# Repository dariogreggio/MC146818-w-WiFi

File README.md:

# MC146818-w-WiFi
a small board, pin compatible to MC146818 RTC, featuring WiFi for retrieving time!

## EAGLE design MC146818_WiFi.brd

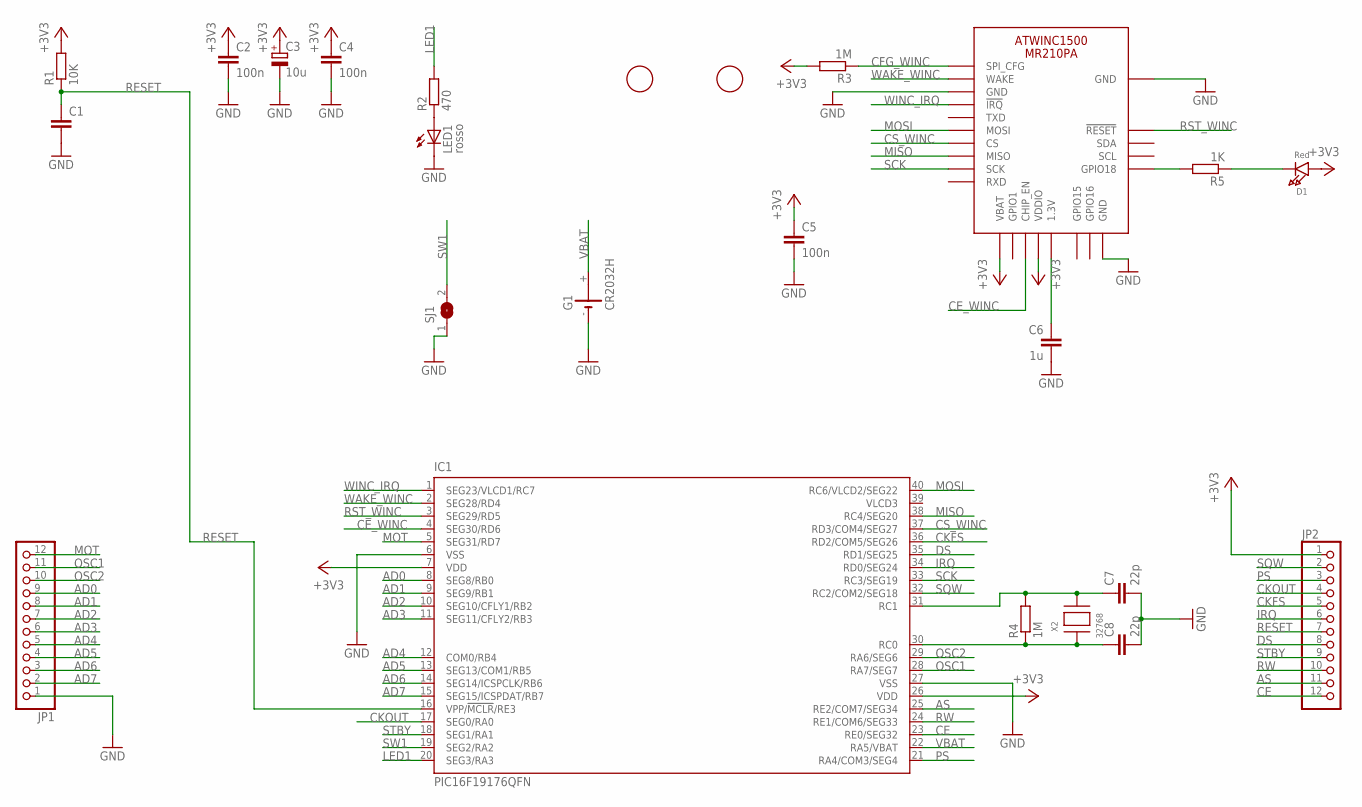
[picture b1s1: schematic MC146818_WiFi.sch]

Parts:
C1: C-EUC0603; C0603
C2, C4, C5: 100n; C0603
C3: 10u; SMC_Z
C6: 1u; C0805
C7, C8: 22p; C0603
D1: Red; CHIPLED_0805_NOOUTLINE
F1, F2: FIDUCIAL; FIDUCIAL_1MM
G1: CR2032H
IC1: PIC16F19176QFN; UQFN40ML5X5MM
JP1, JP2: PINHD-1X12_2.54; 1X12
LED1: rosso; CHIPLED_0805
R1: 10K; R0603
R2: 470; R0603
R3, R4: 1M; R0603
R5: 1K; R0603
SJ1: SJ
X1: ATWINC1500_MR210PB; ATWINC1500_MR210PA
X2: 32768; XTAL3215

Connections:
+3V3: C2.1, C3.+, C4.1, C5.1, D1.A, IC1.7 (VDD), IC1.26 (VDD), JP2.1, R1.2, R3.2, X1.J20 (VBAT), X1.J23 (VDDIO)
AD0: IC1.8 (SEG8/RB0), JP1.9
AD1: IC1.9 (SEG9/RB1), JP1.8
AD2: IC1.10 (SEG10/CFLY1/RB2), JP1.7
AD3: IC1.11 (SEG11/CFLY2/RB3), JP1.6
AD4: IC1.12 (COM0/RB4), JP1.5
AD5: IC1.13 (SEG13/COM1/RB5), JP1.4
AD6: IC1.14 (SEG14/ICSPCLK/RB6), JP1.3
AD7: IC1.15 (SEG15/ICSPDAT/RB7), JP1.2
AS: IC1.25 (RE2/COM7/SEG34), JP2.11
CE: IC1.23 (RE0/SEG32), JP2.12
CE_WINC: IC1.4 (SEG30/RD6), X1.J22 (CHIP_EN)
CFG_WINC: R3.1, X1.J10 (SPI_CFG)
CKFS: IC1.36 (RD2/COM5/SEG26), JP2.5
CKOUT: IC1.17 (SEG0/RA0), JP2.4
CS_WINC: IC1.37 (RD3/COM4/SEG27), X1.J16 (CS)
DS: IC1.35 (RD1/SEG25), JP2.8
GND: C1.2, C2.2, C3.-, C4.2, C5.2, C6.2, C7.2, C8.2, G1.-, IC1.6 (VSS), IC1.27 (VSS), JP1.1, LED1.C, SJ1.1, X1.J9 (GND), X1.J12 (GND), X1.J28 (GND), X1.MTGND (GND)
IRQ: IC1.34 (RD0/SEG24), JP2.6
LED1: IC1.20 (SEG3/RA3), R2.2
MISO: IC1.38 (RC4/SEG20), X1.J17 (MISO)
MOSI: IC1.40 (RC6/VLCD2/SEG22), X1.J15 (MOSI)
MOT: IC1.5 (SEG31/RD7), JP1.12
unnamed: LED1.A, R2.1
unnamed: R5.2, X1.J1 (GPIO18)
unnamed: D1.C, R5.1
unnamed: C6.1, X1.J24 (1.3V)
OSC1: IC1.28 (RA7/SEG7), JP1.11
OSC2: IC1.29 (RA6/SEG6), JP1.10
PS: IC1.21 (RA4/COM3/SEG4), JP2.3
RESET: C1.1, IC1.16 (VPP/!MCLR!/RE3), JP2.7, R1.1
RST_WINC: IC1.3 (SEG29/RD5), X1.J4 (!RESET)
RW: IC1.24 (RE1/COM6/SEG33), JP2.10
SCK: IC1.33 (RC3/SEG19), X1.J18 (SCK)
SOSCI: C8.1, IC1.30 (RC0), R4.1, X2.P$1
SOSCO: C7.1, IC1.31 (RC1), R4.2, X2.P$2
SQW: IC1.32 (RC2/COM2/SEG18), JP2.2
STBY: IC1.18 (SEG1/RA1), JP2.9
SW1: IC1.19 (SEG2/RA2), SJ1.2
VBAT: G1.+, IC1.22 (RA5/VBAT)
WAKE_WINC: IC1.2 (SEG28/RD4), X1.J11 (WAKE)
WINC_IRQ: IC1.1 (SEG23/VLCD1/RC7), X1.J13 (!IRQ)

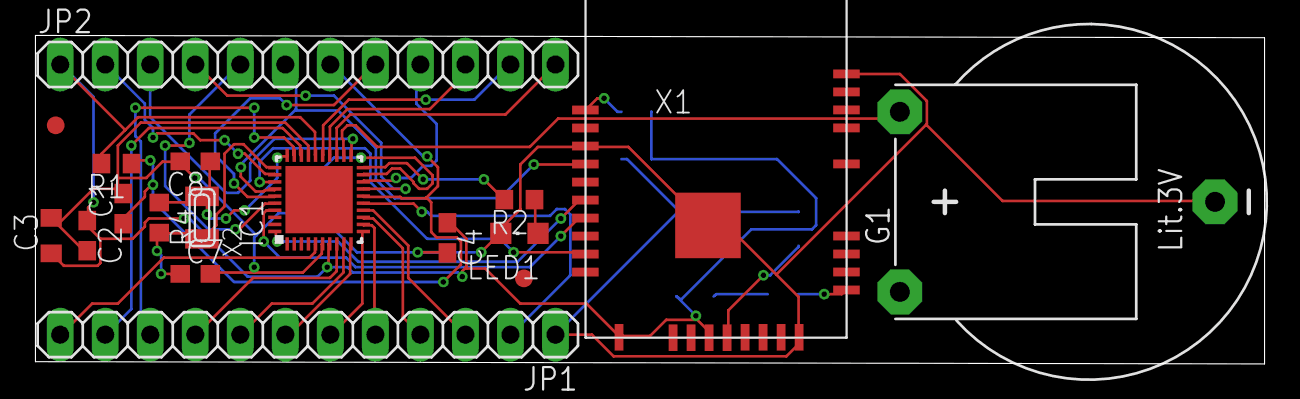
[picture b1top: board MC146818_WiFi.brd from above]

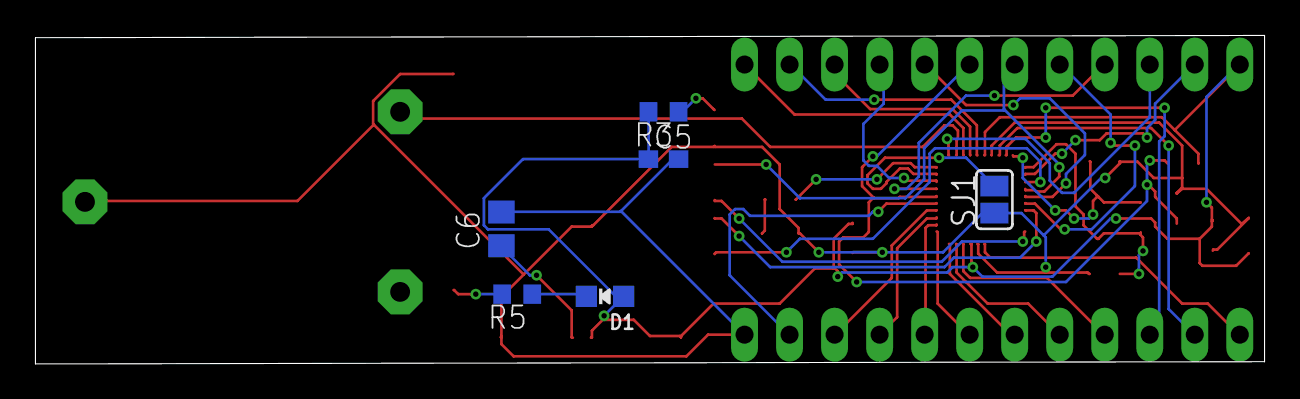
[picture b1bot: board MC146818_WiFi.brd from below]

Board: 2 copper layers, 69.3 x 18.5 mm, 24 parts (6 on the bottom side), 42 nets.

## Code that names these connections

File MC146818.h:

/* 
 * File:   MC146818.h
 * Author: dario
 *
 * Created on 16 marzo 2022, 13.57
 */

#ifndef MC146818_H
#define	MC146818_H

#ifdef	__cplusplus
extern "C" {
#endif

    
#define _XTAL_FREQ 32000000UL
#define VERNUMH 0
#define VERNUML 2

typedef unsigned char BYTE;
typedef unsigned int WORD;
typedef unsigned long DWORD;
typedef unsigned char BOOL;

enum { FALSE=0,TRUE=1 };

#define MAKEWORD(a, b)   ((WORD) (((BYTE) (a)) | ((WORD) ((BYTE) (b))) << 8)) 
#define MAKELONG(a, b)   ((unsigned long) (((WORD) (a)) | ((DWORD) ((WORD) (b))) << 16)) 
//#define HIBYTE(w)   ((BYTE) ((((WORD) (w)) >> 8) /* & 0xFF*/)) 
#define HIBYTE(w)   ((BYTE) (*((char *)&w+1)))		// molto meglio :)
#define HIWORD(l)   ((WORD) (((DWORD) (l) >> 16) & 0xFFFF)) 
#define LOBYTE(w)   ((BYTE) (w)) 
#define LOWORD(l)   ((WORD) (l)) 

typedef struct {
    unsigned char   weekday;    // 
    unsigned char   mday;       // 
    unsigned char   mon;        // 
    unsigned short  year;       // 
	} PIC16_DATE;

typedef struct {
    unsigned char   sec;        // BCD codification for seconds, 00-59
    unsigned char   min;        // BCD codification for minutes, 00-59
    unsigned char   hour;       // BCD codification for hours, 00-24
	} PIC16_TIME;

void UserInit(void);
void Timer_Init(void);
void PWM_Init(void);
void RTCC_Init(void);
void SetTimeFromNow(DWORD,PIC16_DATE *,PIC16_TIME *);
DWORD PIC16RTCCGetDate(void);
DWORD PIC16RTCCGetTime(void);
void PIC16RTCCSetDate(WORD xx_year, WORD month_day);
void PIC16RTCCSetTime(WORD weekDay_hours, WORD minutes_seconds);
void PIC16RTCCSetAlarm(BYTE month, BYTE day, BYTE hours, BYTE minutes, BYTE seconds);
void UnlockRTCC(void);
void LockRTCC(void);

BYTE to_bcd(BYTE);
BYTE from_bcd(BYTE);

    
/** LED ************************************************************/
#define mInitAllLEDs()      LATA &= 0xF7; TRISA &= 0xF7; 

#define mLED_1              LATAbits.LATA3     // pin 20
#define mGetLED_1()         mLED_1
#define mLED_1_On()         mLED_1 = 1;
#define mLED_1_Off()        mLED_1 = 0;
#define mLED_1_Toggle()     mLED_1 = !mLED_1;

    
/** SWITCH *********************************************************/
#define mInitSwitch1()      TRISAbits.TRISA2=1;

#define mInitAllSwitches()  mInitSwitch1(); WPUAbits.WPUA2=1;
#define sw1                 PORTAbits.RA2

    
// PORT B=bus dati/indirizzo
#define	SPISCKTris TRISCbits.TRISC3			// SCK
#define	SPISDITris TRISCbits.TRISC4         // SDI
#define	SPISDOTris TRISCbits.TRISC6			// SDO
#define	SPICSTris  TRISDbits.TRISD3         // CS WiFi
#define	WINCResetTris  TRISDbits.TRISD5     // 
#define	WINCWakeTris  TRISDbits.TRISD4     // 
#define	WINCIRQTris  TRISCbits.TRISC7     // pin 1
	
#define	m_SPISCKBit LATCbits.LATC3		// pin 33
#define	m_SPISDIBit PORTCbits.RC4		// pin 38
#define	m_SPISDOBit LATCbits.LATC6		// pin 40
#define	m_SPICSBit  LATDbits.LATD3
#define	m_WINCResetBit  LATDbits.LATD5
#define	m_WINCWakeBit  LATDbits.LATD4
#define SPIOUT      m_SPISDOBit 
#define SPIIN       m_SPISDIBit
#define SPICLOCK    SPISCKTris
#define SPIENABLE   m_SPIWCSBit

#define m_CE PORTEbits.RE0		// pin 32
#define m_AS PORTEbits.RE2   		// pin 25
#define m_DS PORTDbits.RD1  		// pin 35
#define m_RW PORTEbits.RE1         // pin 24
#define m_STBY PORTAbits.RA1         // pin 18
#define m_IRQ LATDbits.LATD0         // pin 34

#define m_CKFS PORTDbits.RD2         // pin 36
#define m_CKOUT LATAbits.LATA0         // pin 17

#define m_MOT PORTDbits.RD7         // pin 5
#define m_PS  PORTAbits.RA4         // pin 21
#define m_SQW LATCbits.LATC2         // pin 32 PWM

#ifdef	__cplusplus
}
#endif

#endif	/* MC146818_H */

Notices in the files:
parts and their libraries:
microbuilder: This work is placed in the public domain, and may be freely used for commercial and non-commercial work with the following conditions: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
